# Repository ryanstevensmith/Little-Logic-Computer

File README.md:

# Little Logic Computer
 A little personal project, building an 8 bit computer similar to the designs of Ben Eater, but using the TI little logic gates series.

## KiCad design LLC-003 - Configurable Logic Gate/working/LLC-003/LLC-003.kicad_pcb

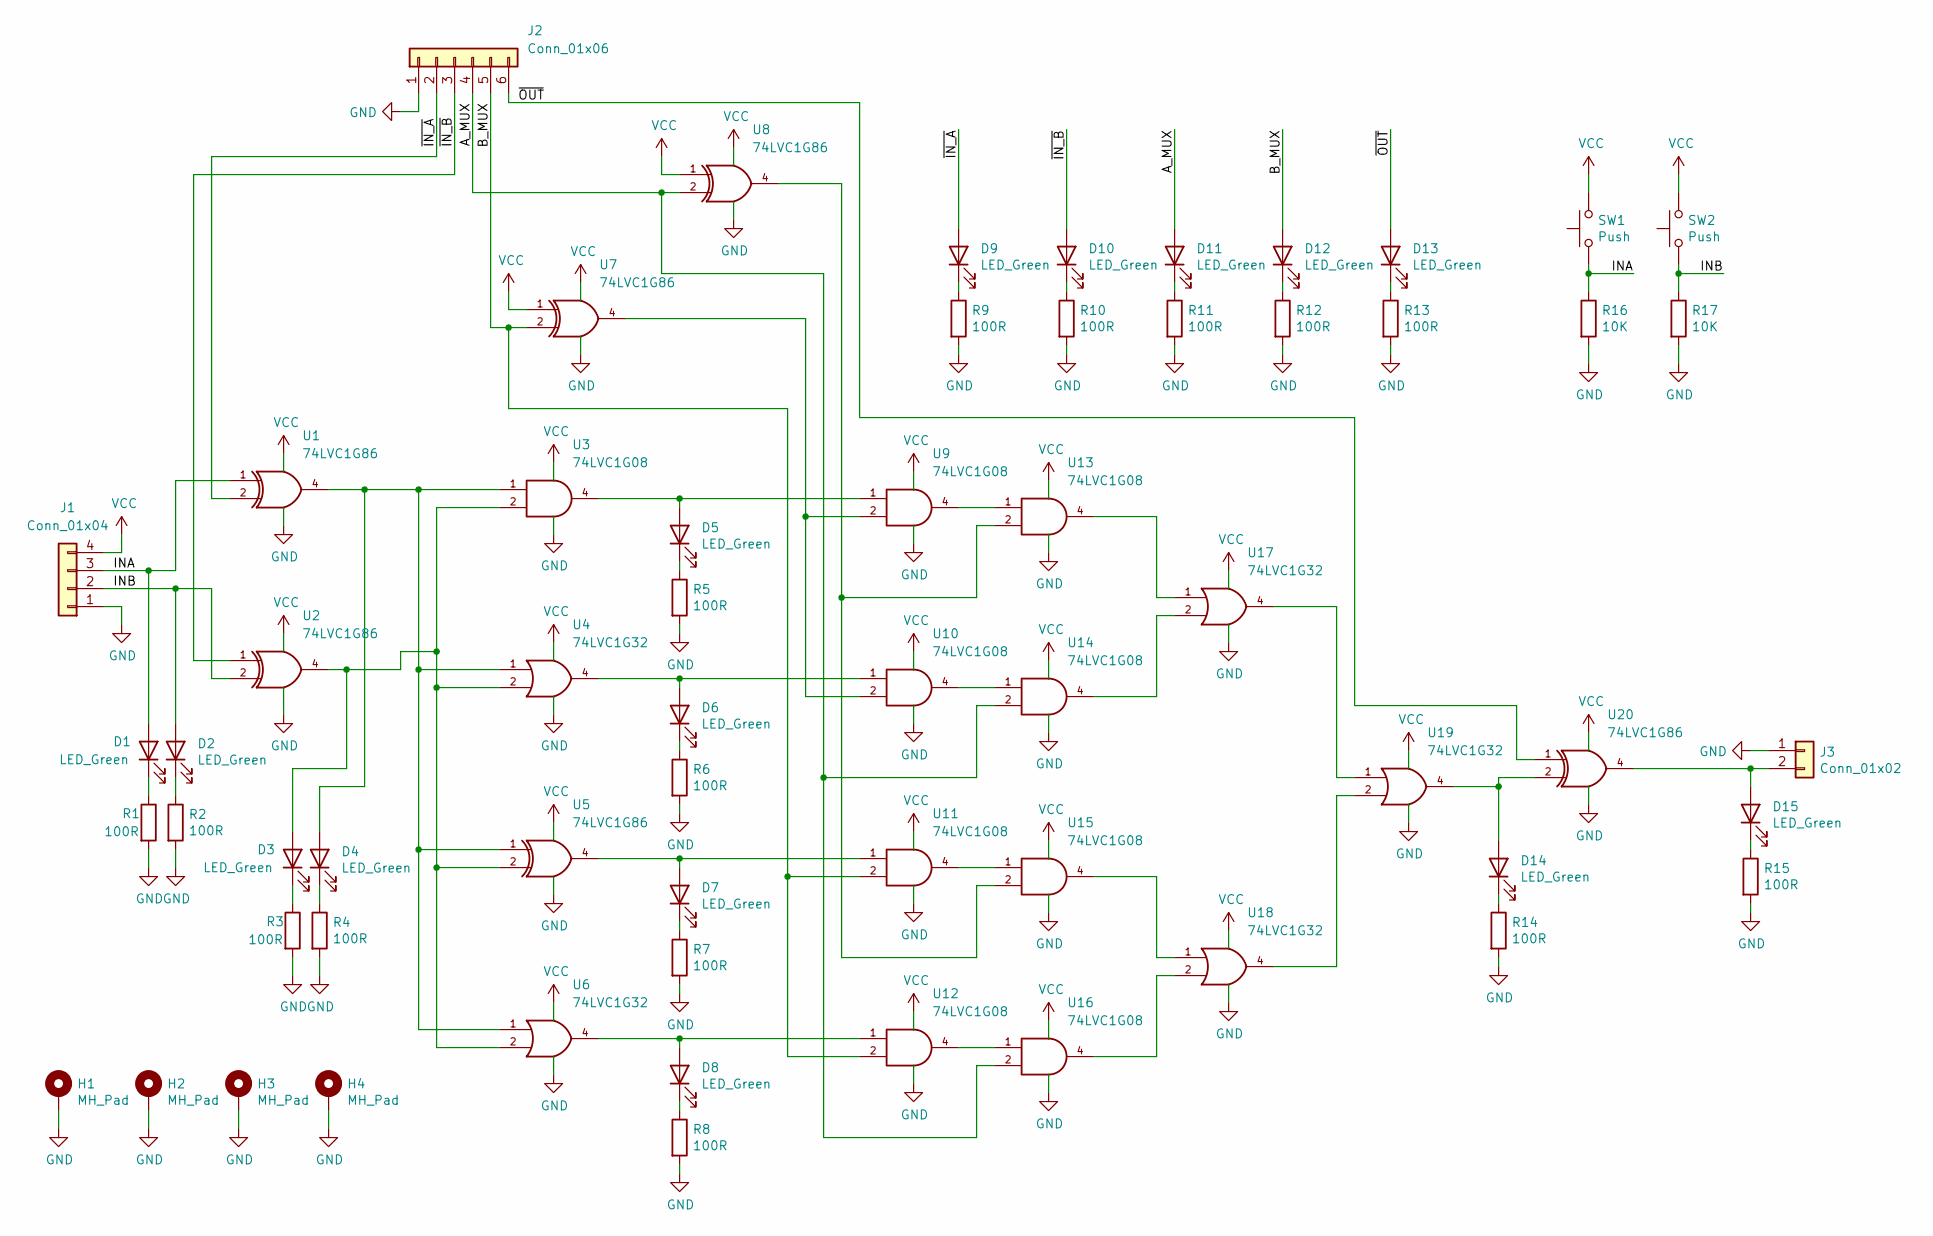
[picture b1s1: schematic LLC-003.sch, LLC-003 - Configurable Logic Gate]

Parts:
D1, D2, D3, D4, D5, D6, D7, D8, D9, D10, D11, D12, D13, D14, D15: LED_Green; LED_0603_1608Metric; Part Number APT1608SGC
H1, H2, H3, H4: MH_Pad; MountingHole_3.2mm_M3_Pad_Via; Part Number n/a
J1: Conn_01x04; PinHeader_1x04_P2.54mm_Vertical; Part Number 22-28-4041
J2: Conn_01x06; PinHeader_1x06_P2.54mm_Vertical; Part Number 22-28-4061
J3: Conn_01x02; PinHeader_1x02_P2.54mm_Vertical; Part Number 22-28-4022
R1, R2, R3, R4, R5, R6, R7, R8, R9, R10, R11, R12, R13, R14, R15: 100R; R_0603_1608Metric; Part Number CRCW0603100RFKEAHP
R16, R17: 10K; R_0603_1608Metric; Part Number CRCW060310K0FKEAHP
SW1, SW2: Push; SW_SPST_PTS645; Part Number PTS645VK832LFS
U1, U2, U5, U7, U8, U20: 74LVC1G86; SOT-23-5; Part Number SN74LVC1G86DBVR
U3, U9, U10, U11, U12, U13, U14, U15, U16: 74LVC1G08; SOT-23-5; Part Number SN74LVC1G08DBVR
U4, U6, U17, U18, U19: 74LVC1G32; SOT-23-5; Part Number SN74LVC1G32DBVR

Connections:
/A_MUX: D11.2 (A), J2.4, U8.2, U14.2, U16.2
/B_MUX: D12.2 (A), J2.5, U7.2, U11.2, U12.2
/INA: D1.2 (A), J1.3, R16.1, SW1.1, U1.1
/INB: D2.2 (A), J1.2, R17.1, SW2.1, U2.2
/~IN_A: D9.2 (A), J2.2, U1.2
/~IN_B: D10.2 (A), J2.3, U2.1
/~OUT: D13.2 (A), J2.6, U20.1
GND: H1.1, H2.1, H3.1, H4.1, J1.1, J2.1, J3.1, R1.2, R2.2, R3.2, R4.2, R5.2, R6.2, R7.2, R8.2, R9.2, R10.2, R11.2, R12.2, R13.2, R14.2, R15.2, R16.2, R17.2, U1.3 (GND), U2.3 (GND), U3.3 (GND), U4.3 (GND), U5.3 (GND), U6.3 (GND), U7.3 (GND), U8.3 (GND), U9.3 (GND), U10.3 (GND), U11.3 (GND), U12.3 (GND), U13.3 (GND), U14.3 (GND), U15.3 (GND), U16.3 (GND), U17.3 (GND), U18.3 (GND), U19.3 (GND), U20.3 (GND)
unnamed: D1.1 (K), R1.1
unnamed: D2.1 (K), R2.1
unnamed: D3.1 (K), R3.1
unnamed: D3.2 (A), U2.4, U3.2, U4.2, U5.2, U6.2
unnamed: D4.1 (K), R4.1
unnamed: D4.2 (A), U1.4, U3.1, U4.1, U5.1, U6.1
unnamed: D5.1 (K), R5.1
unnamed: D5.2 (A), U3.4, U9.1
unnamed: D6.1 (K), R6.1
unnamed: D6.2 (A), U4.4, U10.1
unnamed: D7.1 (K), R7.1
unnamed: D7.2 (A), U5.4, U11.1
unnamed: D8.1 (K), R8.1
unnamed: D8.2 (A), U6.4, U12.1
unnamed: D9.1 (K), R9.1
unnamed: D10.1 (K), R10.1
unnamed: D11.1 (K), R11.1
unnamed: D12.1 (K), R12.1
unnamed: D13.1 (K), R13.1
unnamed: D14.1 (K), R14.1
unnamed: D14.2 (A), U19.4, U20.2
unnamed: D15.1 (K), R15.1
unnamed: D15.2 (A), J3.2, U20.4
unnamed: U7.4, U9.2, U10.2
unnamed: U10.4, U14.1
unnamed: U11.4, U15.1
unnamed: U12.4, U16.1
unnamed: U9.4, U13.1
unnamed: U8.4, U13.2, U15.2
unnamed: U13.4, U17.1
unnamed: U14.4, U17.2
unnamed: U15.4, U18.1
unnamed: U16.4, U18.2
unnamed: U17.4, U19.1
unnamed: U18.4, U19.2
VCC: J1.4, SW1.2, SW2.2, U1.5 (VCC), U2.5 (VCC), U3.5 (VCC), U4.5 (VCC), U5.5 (VCC), U6.5 (VCC), U7.1, U7.5 (VCC), U8.1, U8.5 (VCC), U9.5 (VCC), U10.5 (VCC), U11.5 (VCC), U12.5 (VCC), U13.5 (VCC), U14.5 (VCC), U15.5 (VCC), U16.5 (VCC), U17.5 (VCC), U18.5 (VCC), U19.5 (VCC), U20.5 (VCC)

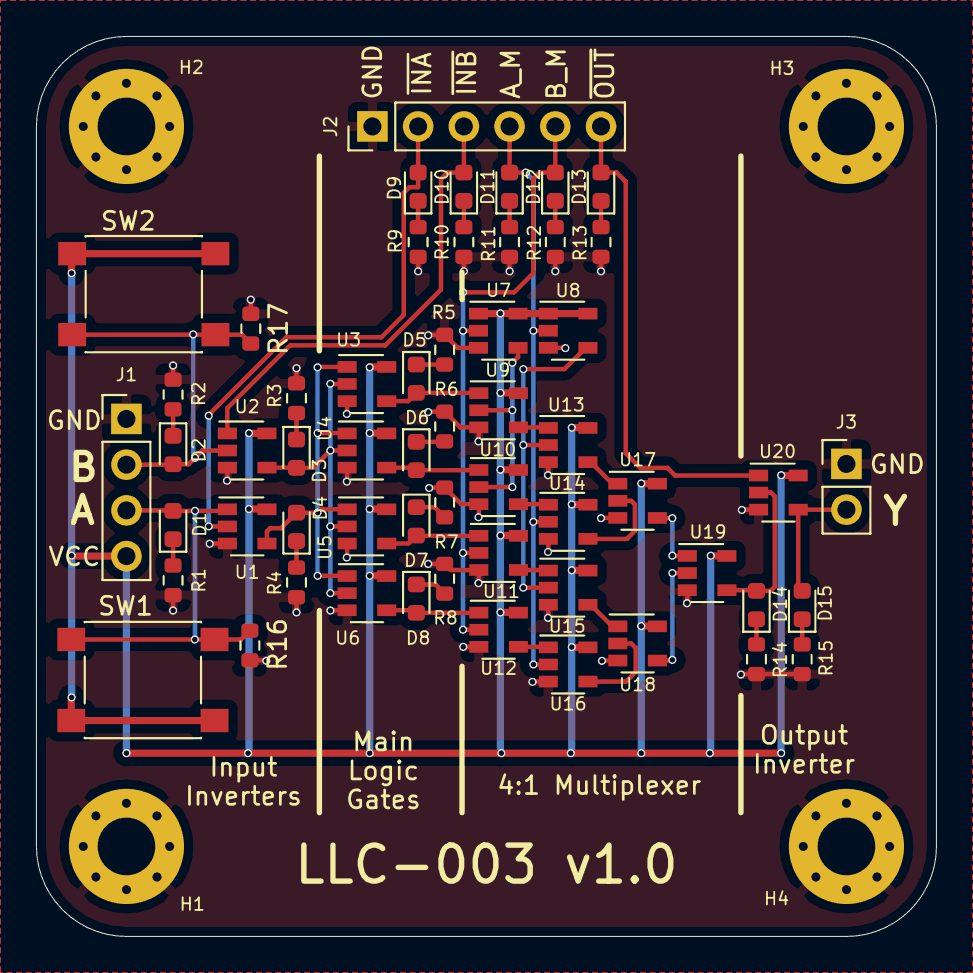
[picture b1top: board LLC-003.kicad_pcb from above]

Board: 2 copper layers, 50.0 x 50.0 mm, 61 parts (0 on the bottom side), 44 nets.

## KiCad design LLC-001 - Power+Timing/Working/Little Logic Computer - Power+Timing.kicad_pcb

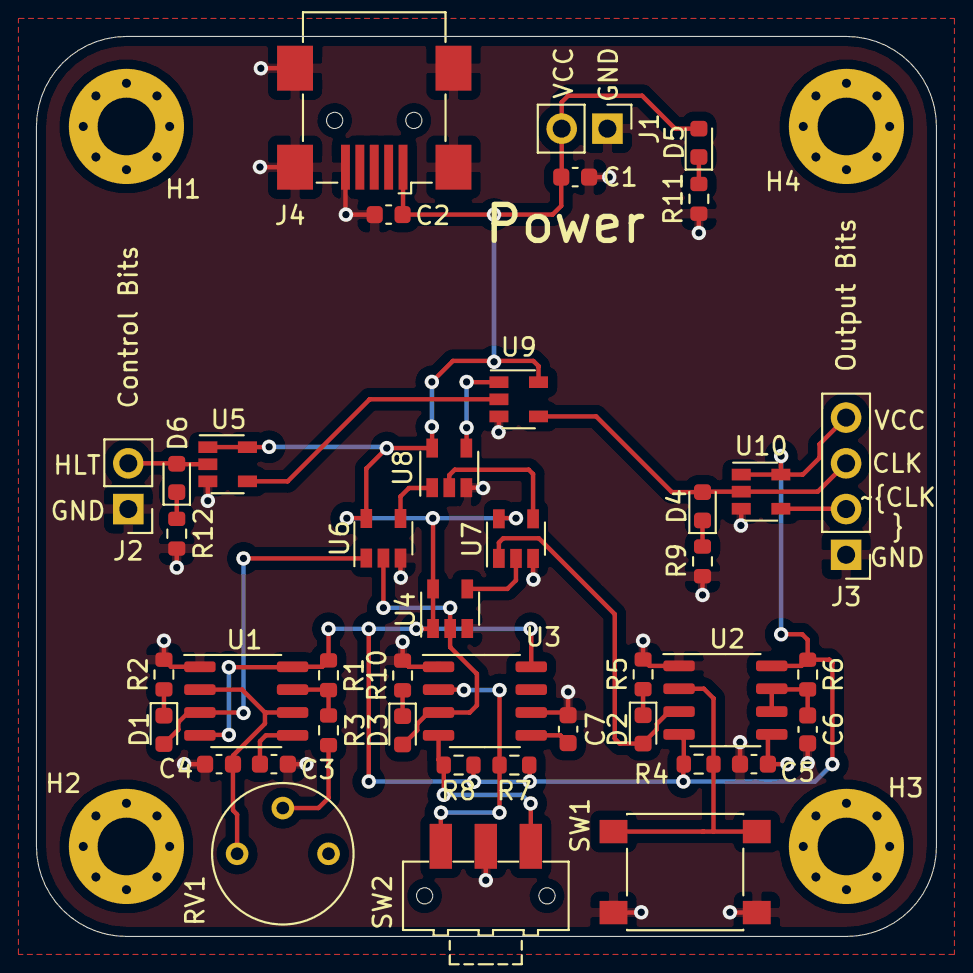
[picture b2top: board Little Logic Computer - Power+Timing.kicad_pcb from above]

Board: 2 copper layers, 50.0 x 50.0 mm, 46 parts (0 on the bottom side), 29 nets.

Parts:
C1, C2, C6: 100n; C_0603_1608Metric
C3, C5, C7: 10n; C_0603_1608Metric
C4: 1u; C_0603_1608Metric
D1, D2, D3, D4, D6: LED_Green; LED_0603_1608Metric
D5: LED_Red; LED_0603_1608Metric
H1, H2, H3, H4: MountingHole; MountingHole_3.2mm_M3_Pad_Via
J1, J2: Conn_01x02; PinHeader_1x02_P2.54mm_Vertical
J3: Conn_01x04; PinHeader_1x04_P2.54mm_Vertical
J4: USB_B_Mini; USB_Mini-B_Wuerth_65100516121_Horizontal
R1, R3, R4, R7, R8: 1K; R_0603_1608Metric
R2, R5, R9, R10, R11, R12: 330R; R_0603_1608Metric
R6: 1M; R_0603_1608Metric
RV1: 1M; Potentiometer_Bourns_3339P_Vertical
SW1: SW_Push; SW_SPST_PTS645
SW2: SW_SPDT; SW_SPDT_CK-JS102011SAQN
U1, U2, U3: LM555; SO-8_3.9x4.9mm_P1.27mm
U4, U5, U10: 74LVC1G86; SOT-23-5
U6, U7, U9: 74LVC1G08; SOT-23-5
U8: 74LVC1G32; SOT-23-5

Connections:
/CLK: D4.2, J3.3, U9.4, U10.2
/HLT: D6.2, J2.2, U5.2
/~CLK: J3.2, U10.4
GND: C1.2, C2.2, C3.2, C4.2, C5.2, C6.2, C7.2, J1.1, J2.1, J3.1, J4.5, J4.6, R2.2, R5.2, R9.1, R10.2, R11.1, R12.1, SW1.1, SW2.2, U1.1, U2.1, U3.1, U3.6, U4.3, U5.3, U6.3, U7.3, U8.3, U9.3, U10.3
unnamed: C3.1, U1.5
unnamed: C4.1, RV1.1, U1.2, U1.6
unnamed: C5.1, U2.5
unnamed: C6.1, R6.2, U2.6, U2.7
unnamed: C7.1, U3.5
unnamed: D1.1, R2.1
unnamed: D1.2, U1.3, U6.1
unnamed: D2.1, R5.1
unnamed: D2.2, U2.3, U7.1
unnamed: D3.1, R10.1
unnamed: D3.2, U3.3, U4.2, U6.2
unnamed: D4.1, R9.2
unnamed: D5.1, R11.2
unnamed: D6.1, R12.2
unnamed: R1.2, R3.2, U1.7
unnamed: R3.1, RV1.2
unnamed: R4.1, SW1.2, U2.2
unnamed: R7.2, SW2.1, U3.2
unnamed: R8.2, SW2.3, U3.4
unnamed: U4.4, U7.2
unnamed: U5.4, U9.2
unnamed: U6.4, U8.1
unnamed: U7.4, U8.2
unnamed: U8.4, U9.1
VCC: C1.1, C2.1, D5.2, J1.2, J3.4, J4.1, R1.1, R4.2, R6.1, R7.1, R8.1, U1.4, U1.8, U2.4, U2.8, U3.8, U4.1, U4.5, U5.1, U5.5, U6.5, U7.5, U8.5, U9.5, U10.1, U10.5

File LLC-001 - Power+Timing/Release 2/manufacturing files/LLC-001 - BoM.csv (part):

"Source:","C:\Users\rti97923\OneDrive - Science and Technology Facilities Council\Personal projects\Little Logic Computer\LLC-001 - Power+Timing\Working\Little Logic Computer - Power+Timing.sch"
"Date:","10/05/2021 15:45:03"
"Tool:","Eeschema (5.1.9)-1"
"Generator:","C:\Program Files\KiCad\bin\scripting\plugins/bom_csv_grouped_by_value.py"
"Component Count:","46"

"Individual Components:"

"Item","Qty","Reference(s)","Value","LibPart","Footprint","Datasheet","Description","Generic Part","Height","Manufacturer","Manufacturer_Name","Manufacturer_Part_Number","Part Number"
"","","C1","100n","KEMET_SMD:100n_0603","Capacitor_SMD:C_0603_1608Metric","https://api.kemet.com/component-edge/download/specsheet/C060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","100n, 0603, X7R, 50V","no","","KEMET","","","C0603C104J5RACTU"
"","","C2","100n","KEMET_SMD:100n_0603","Capacitor_SMD:C_0603_1608Metric","https://api.kemet.com/component-edge/download/specsheet/C060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","100n, 0603, X7R, 50V","no","","KEMET","","","C0603C104J5RACTU"
"","","C3","10n","KEMET_SMD:10n_0603","Capacitor_SMD:C_0603_1608Metric","https://api.kemet.com/component-edge/download/specsheet/C060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","10n, 0603, X7R, 50V","no","","KEMET","","","C0603C103J5RACTU"
"","","C4","1u","KEMET_SMD:1u_0603","Capacitor_SMD:C_0603_1608Metric","https://api.kemet.com/component-edge/download/specsheet/C060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","1u, 0603, X7R, 10V","no","","KEMET","","","C0603C105K8RACTU"
"","","C5","10n","KEMET_SMD:10n_0603","Capacitor_SMD:C_0603_1608Metric","https://api.kemet.com/component-edge/download/specsheet/C060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","10n, 0603, X7R, 50V","no","","KEMET","","","C0603C103J5RACTU"
"","","C6","100n","KEMET_SMD:100n_0603","Capacitor_SMD:C_0603_1608Metric","https://api.kemet.com/component-edge/download/specsheet/C060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","100n, 0603, X7R, 50V","no","","KEMET","","","C0603C104J5RACTU"
"","","C7","10n","KEMET_SMD:10n_0603","Capacitor_SMD:C_0603_1608Metric","https://api.kemet.com/component-edge/download/specsheet/C060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","10n, 0603, X7R, 50V","no","","KEMET","","","C0603C103J5RACTU"
"","","D1","LED_Green","Kingbright:LED_Green_0603","LED_SMD:LED_0603_1608Metric","https://www.mouser.co.uk/datasheet/2/216/APT1608SGC-32861.pdf","Green 0603 LED","no","","Kingbright","","","APT1608SGC"
"","","D2","LED_Green","Kingbright:LED_Green_0603","LED_SMD:LED_0603_1608Metric","https://www.mouser.co.uk/datasheet/2/216/APT1608SGC-32861.pdf","Green 0603 LED","no","","Kingbright","","","APT1608SGC"
"","","D3","LED_Green","Kingbright:LED_Green_0603","LED_SMD:LED_0603_1608Metric","https://www.mouser.co.uk/datasheet/2/216/APT1608SGC-32861.pdf","Green 0603 LED","no","","Kingbright","","","APT1608SGC"
"","","D4","LED_Green","Kingbright:LED_Green_0603","LED_SMD:LED_0603_1608Metric","https://www.mouser.co.uk/datasheet/2/216/APT1608SGC-32861.pdf","Green 0603 LED","no","","Kingbright","","","APT1608SGC"
"","","D5","LED_Red","Kingbright:LED_Red_0603","LED_SMD:LED_0603_1608Metric","https://www.mouser.co.uk/datasheet/2/216/APT1608SRCPRV-226086.pdf","Red 0603 LED","no","","Kingbright","","","APT1608SRCPRV"
"","","D6","LED_Green","Kingbright:LED_Green_0603","LED_SMD:LED_0603_1608Metric","https://www.mouser.co.uk/datasheet/2/216/APT1608SGC-32861.pdf","Green 0603 LED","no","","Kingbright","","","APT1608SGC"
"","","H1","MountingHole","Mechanical:MountingHole","MountingHole:MountingHole_3.2mm_M3_Pad_Via","~","","","","","","",""
"","","H2","MountingHole","Mechanical:MountingHole","MountingHole:MountingHole_3.2mm_M3_Pad_Via","~","","","","","","",""
"","","H3","MountingHole","Mechanical:MountingHole","MountingHole:MountingHole_3.2mm_M3_Pad_Via","~","","","","","","",""
"","","H4","MountingHole","Mechanical:MountingHole","MountingHole:MountingHole_3.2mm_M3_Pad_Via","~","","","","","","",""
"","","J1","Conn_01x02","Connector_Generic:Conn_01x02","Connector_PinHeader_2.54mm:PinHeader_1x02_P2.54mm_Vertical","~","","","","","","",""
"","","J2","Conn_01x02","Connector_Generic:Conn_01x02","Connector_PinHeader_2.54mm:PinHeader_1x02_P2.54mm_Vertical","~","","","","","","",""
"","","J3","Conn_01x04","Connector_Generic:Conn_01x04","Connector_PinHeader_2.54mm:PinHeader_1x04_P2.54mm_Vertical","~","","","","","","",""
"","","J4","USB_B_Mini","Ryans_kicad_lib:USB_B_Mini","Connector_USB:USB_Mini-B_Wuerth_65100516121_Horizontal","https://datasheet.lcsc.com/szlcsc/1811141116_Korean-Hroparts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","USB Connector, Mini USB Type B, USB 2.0, Receptacle, 5 Ways, Surface Mount, Right Angle","no","4.1","Korean Hroparts Elec","WURTH ELEKTRONIK","65100516121","U-M-M5SS-W-2"
"","","R1","1K","Vishay_Res_SMD:1K_0603","Resistor_SMD:R_0603_1608Metric","https://www.vishay.com/docs/20043/crcwhpe3.pdf","1K, 0603, 1%, 0.33W","no","","Vishay","","","CRCW06031K00FKEAHP"
"","","R2","330R","Vishay_Res_SMD:330R_0603","Resistor_SMD:R_0603_1608Metric","https://www.vishay.com/docs/20043/crcwhpe3.pdf","330R, 0603, 1%, 0.33W","no","","Vishay","","","CRCW0603330RFKEAHP"
"","","R3","1K","Vishay_Res_SMD:1K_0603","Resistor_SMD:R_0603_1608Metric","https://www.vishay.com/docs/20043/crcwhpe3.pdf","1K, 0603, 1%, 0.33W","no","","Vishay","","","CRCW06031K00FKEAHP"
"","","R4","1K","Vishay_Res_SMD:1K_0603","Resistor_SMD:R_0603_1608Metric","https://www.vishay.com/docs/20043/crcwhpe3.pdf","1K, 0603, 1%, 0.33W","no","","Vishay","","","CRCW06031K00FKEAHP"
"","","R5","330R","Vishay_Res_SMD:330R_0603","Resistor_SMD:R_0603_1608Metric","https://www.vishay.com/docs/20043/crcwhpe3.pdf","330R, 0603, 1%, 0.33W","no","","Vishay","","","CRCW0603330RFKEAHP"
"","","R6","1M","Vishay_Res_SMD:1M_0603","Resistor_SMD:R_0603_1608Metric","https://www.vishay.com/docs/20043/crcwhpe3.pdf","1M, 0603, 1%, 0.33W","no","","Vishay","","","CRCW06031M00FKEAHP"
"","","R7","1K","Vishay_Res_SMD:1K_0603","Resistor_SMD:R_0603_1608Metric","https://www.vishay.com/docs/20043/crcwhpe3.pdf","1K, 0603, 1%, 0.33W","no","","Vishay","","","CRCW06031K00FKEAHP"
"","","R8","1K","Vishay_Res_SMD:1K_0603","Resistor_SMD:R_0603_1608Metric","https://www.vishay.com/docs/20043/crcwhpe3.pdf","1K, 0603, 1%, 0.33W","no","","Vishay","","","CRCW06031K00FKEAHP"
"","","R9","330R","Vishay_Res_SMD:330R_0603","Resistor_SMD:R_0603_1608Metric","https://www.vishay.com/docs/20043/crcwhpe3.pdf","330R, 0603, 1%, 0.33W","no","","Vishay","","","CRCW0603330RFKEAHP"
"","","R10","330R","Vishay_Res_SMD:330R_0603","Resistor_SMD:R_0603_1608Metric","https://www.vishay.com/docs/20043/crcwhpe3.pdf","330R, 0603, 1%, 0.33W","no","","Vishay","","","CRCW0603330RFKEAHP"
"","","R11","330R","Vishay_Res_SMD:330R_0603","Resistor_SMD:R_0603_1608Metric","https://www.vishay.com/docs/20043/crcwhpe3.pdf","330R, 0603, 1%, 0.33W","no","","Vishay","","","CRCW0603330RFKEAHP"
"","","R12","330R","Vishay_Res_SMD:330R_0603","Resistor_SMD:R_0603_1608Metric","https://www.vishay.com/docs/20043/crcwhpe3.pdf","330R, 0603, 1%, 0.33W","no","","Vishay","","","CRCW0603330RFKEAHP"
"","","RV1","1M","Device:R_POT","Potentiometer_THT:Potentiometer_Bourns_3339P_Vertical","https://datasheet.lcsc.com/szlcsc/1810170824_BOCHEN-Chengdu-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","1M ±10% ±250ppm/℃ 3323P Precision Potentiometer RoHS","no","","BOCHEN","","","3323P-1-105"
"","","SW1","SW_Push","Switch:SW_Push","Button_Switch_SMD:SW_SPST_PTS645","https://datasheet.lcsc.com/szlcsc/1912111437_C-K-PTS645VK832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","Tactile Switches small sized s Light Touch Switch","yes","","C&K","","","PTS645VK832LFS"
"","","SW2","SW_SPDT","Switch:SW_SPDT","Button_Switch_SMD:SW_SPDT_CK-JS102011SAQN","https://datasheet.lcsc.com/szlcsc/2004181004_Yuandi-TA-3525-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","SMD,9.1x3.5x4.0mm Toggle Switches RoHS","yes","","Yuandi","","","TA-3525-A3"
"","","U1","LM555","Little-Logic-Computer---Power+Timing-rescue:LM555-Timer","Package_SO:SO-8_3.9x4.9mm_P1.27mm","http://www.ti.com/lit/ds/symlink/lm555.pdf","Timer SOIC-8_150mil RoHS","yes","","Texas Instruments","","","NE555DR"
"","","U2","LM555","Little-Logic-Computer---Power+Timing-rescue:LM555-Timer","Package_SO:SO-8_3.9x4.9mm_P1.27mm","http://www.ti.com/lit/ds/symlink/lm555.pdf","Timer SOIC-8_150mil RoHS","yes","","Texas Instruments","","","NE555DR"
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
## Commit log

2021-08-18 Initial upload
    Initial upload of files, including the finished design for LLC001 and LLC003.
